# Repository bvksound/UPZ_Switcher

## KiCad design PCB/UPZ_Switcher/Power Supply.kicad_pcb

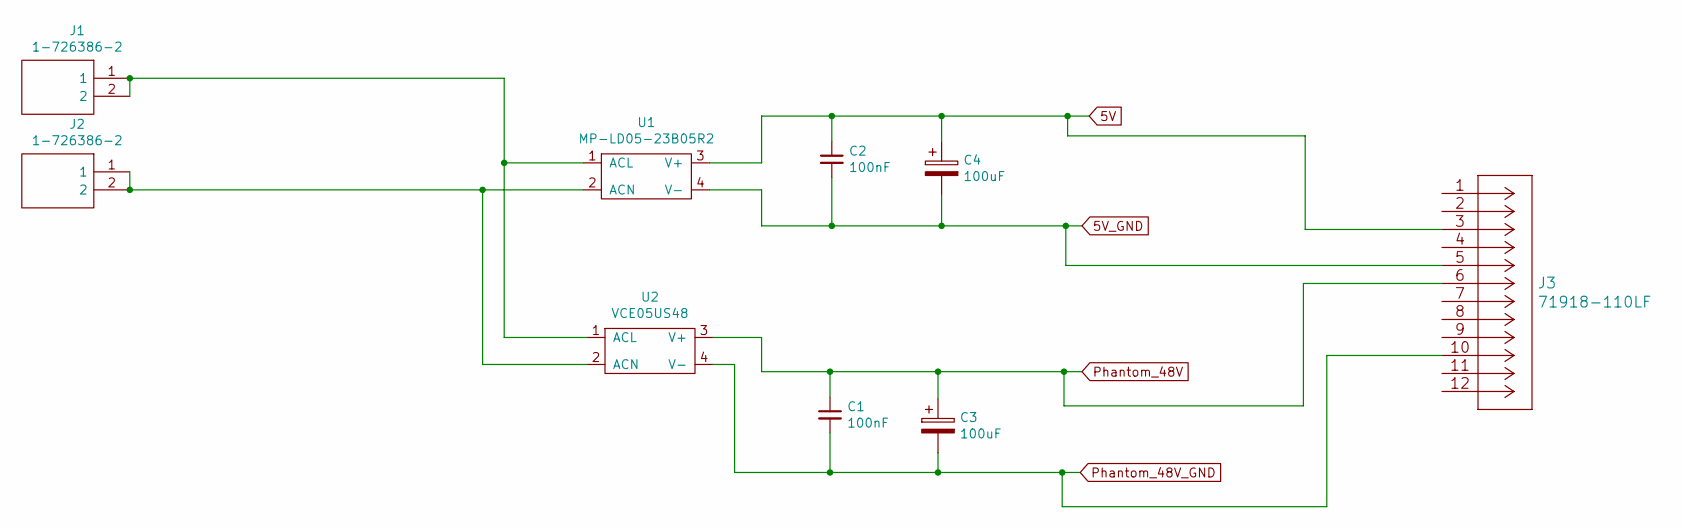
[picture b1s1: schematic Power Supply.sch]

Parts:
C1, C2: 100nF; C_1206_3216Metric
C3, C4: 100uF; CP_Radial_D10.0mm_P5.00mm
J1, J2: 1-726386-2; 17263862; Manufacturer_Part_Number 1-726386-2; Mouser Part Number 571-1-726386-2
J3: 71918-110LF
U1: MP-LD05-23B05R2
U2: VCE05US48

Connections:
5V: C2.1, C4.1, J3.3, U1.3 (V+)
5V_GND: C2.2, C4.2, J3.5, U1.4 (V-)
unnamed: J1.1, J1.2, U1.1 (ACL), U2.1 (ACL)
unnamed: J2.1, J2.2, U1.2 (ACN), U2.2 (ACN)
Phantom_48V: C1.1, C3.1, J3.6, U2.3 (V+)
Phantom_48V_GND: C1.2, C3.2, J3.10, U2.4 (V-)

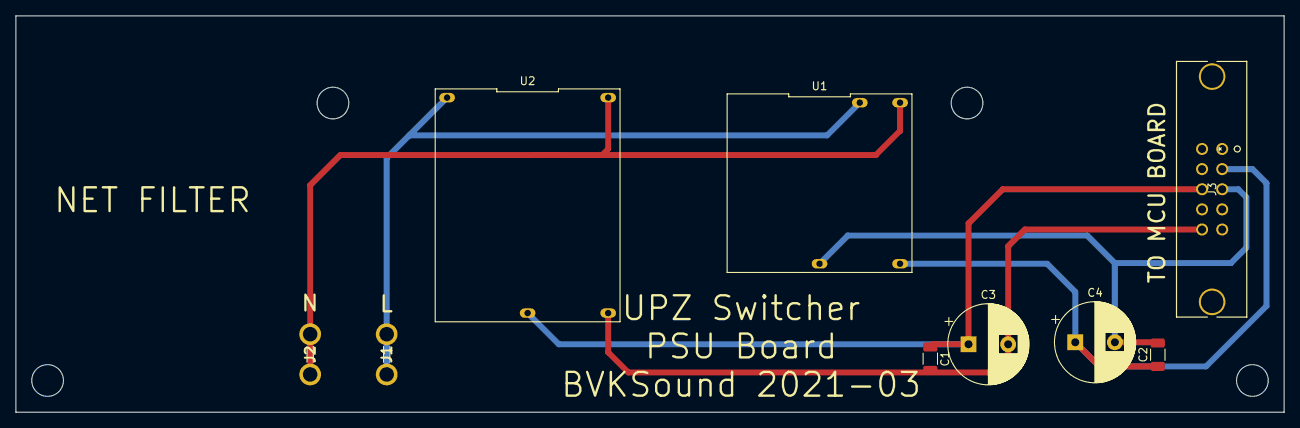
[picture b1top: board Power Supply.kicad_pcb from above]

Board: 2 copper layers, 160.0 x 50.0 mm, 9 parts (0 on the bottom side), 6 nets.

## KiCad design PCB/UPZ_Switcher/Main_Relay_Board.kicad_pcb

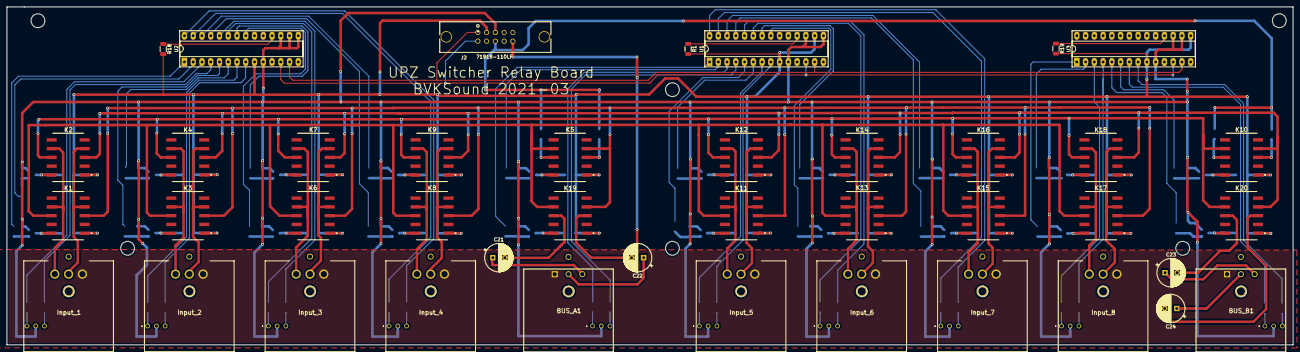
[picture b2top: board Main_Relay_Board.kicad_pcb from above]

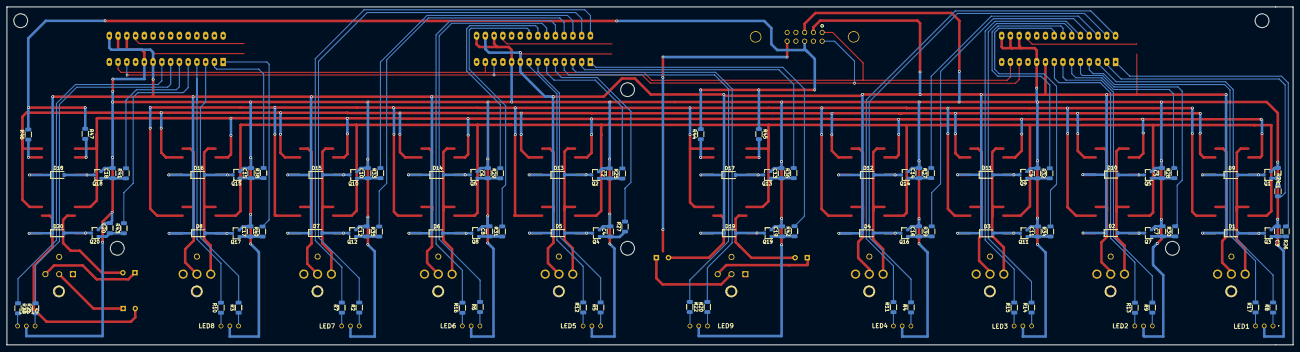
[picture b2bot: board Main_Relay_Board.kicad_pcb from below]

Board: 2 copper layers, 373.0 x 98.0 mm, 155 parts (105 on the bottom side), 141 nets.

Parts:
BUS_A1: NC3MD-H; NC3MDH
BUS_B1: NC3MD-H; NC3MDH
C1, C2, C3, C4, C5, C6, C7, C8, C9, C10, C11, C12, C13, C14, C15, C16, C17, C18, C19, C20: 10nF; C_1206_3216Metric
C21, C22, C23, C24: 47uF; CP_Radial_D8.0mm_P3.50mm
D1, D2, D3, D4, D5, D6, D7, D8, D9, D10, D11, D12, D13, D14, D15, D16, D17, D18, D19, D20: 1N4148W; D_SOD-123
Input_1, Input_2, Input_3, Input_4, Input_5, Input_6, Input_7, Input_8: NC3FDH
J2: 71918-110LF
K1, K2, K3, K4, K5, K6, K7, K8, K9, K10, K11, K12, K13, K14, K15, K16, K17, K18, K19, K20: TQ2SA-5V-Z; TQ2SAL23VZ
LED1, LED2, LED3, LED4, LED5, LED6, LED7, LED8, LED9, LED10: L-115WEGW; L115WEGW
Q1, Q2, Q3, Q4, Q5, Q6, Q7, Q8, Q9, Q10, Q11, Q12, Q13, Q14, Q15, Q16, Q17, Q18, Q19, Q20: BS170F; SOT-23
R1, R18, R19: 10K; R_1206_3216Metric
R2, R3, R4, R5, R6, R7, R8, R9, R10, R11, R12, R13, R14, R15, R16, R17, R20, R21, R22, R23: 100; R_1206_3216Metric
R24, R25, R26, R27, R28, R29, R30, R31, R32, R33, R34, R35, R36, R37, R38, R39, R40, R41, R42, R43: 1K; R_1206_3216Metric
R44, R45, R46, R47: 6K8; R_1206_3216Metric
U1, U2, U3: MCP23017_SP; DIP-28_W7.62mm_Socket_LongPads

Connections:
/Relay/BUSA.2: K1.8, K3.8, K5.7, K6.8, K8.8, K11.8, K13.8, K15.8, K17.8, K19.7
/Relay/BUSA.3: K1.3, K3.3, K5.4, K6.3, K8.3, K11.3, K13.3, K15.3, K17.3, K19.4
/Relay/BUSB.2: K2.8, K4.8, K7.8, K9.8, K10.7, K12.8, K14.8, K16.8, K18.8, K20.7
/Relay/BUSB.3: K2.3, K4.3, K7.3, K9.3, K10.4, K12.3, K14.3, K16.3, K18.3, K20.4
/Relay/IN1.2: Input_1.2, K1.7, K2.7
/Relay/IN1.3: Input_1.3, K1.4, K2.4
/Relay/IN2.2: Input_2.2, K3.7, K4.7
/Relay/IN2.3: Input_2.3, K3.4, K4.4
/Relay/IN3.2: Input_3.2, K6.7, K7.7
/Relay/IN3.3: Input_3.3, K6.4, K7.4
/Relay/IN4.2: Input_4.2, K8.7, K9.7
/Relay/IN4.3: Input_4.3, K8.4, K9.4
/Relay/IN5.2: Input_5.2, K11.7, K12.7
/Relay/IN5.3: Input_5.3, K11.4, K12.4
/Relay/IN6.2: Input_6.2, K13.7, K14.7
/Relay/IN6.3: Input_6.3, K13.4, K14.4
/Relay/IN7.2: Input_7.2, K15.7, K16.7
/Relay/IN7.3: Input_7.3, K15.4, K16.4
/Relay/IN8.2: Input_8.2, K17.7, K18.7
/Relay/IN8.3: Input_8.3, K17.4, K18.4
/Relay/OUTA.2: BUS_A1.2, C21.1
/Relay/OUTA.3: BUS_A1.3, C22.1
/Relay/OUTB.2: BUS_B1.2, C23.1
/Relay/OUTB.3: BUS_B1.3, C24.1
GND: C1.2, C2.2, C3.2, C4.2, C5.2, C6.2, C7.2, C8.2, C9.2, C10.2, C11.2, C12.2, C13.2, C14.2, C15.2, C16.2, C17.2, C18.2, C19.2, C20.2, J2.5, LED1.2, LED2.2, LED3.2, LED4.2, LED5.2, LED6.2, LED7.2, LED8.2, LED9.2, LED10.2, Q1.2, Q2.2, Q3.2, Q4.2, Q5.2, Q6.2, Q7.2, Q8.2, Q9.2, Q10.2, Q11.2, Q12.2, Q13.2, Q14.2, Q15.2, Q16.2, Q17.2, Q18.2, Q19.2, Q20.2, U1.10, U1.15, U1.17, U2.10, U2.15, U2.16, U2.17, U3.10, U3.16, U3.17
I2C_SCK: J2.2, U1.12, U2.12, U3.12
I2C_SDA: J2.1, U1.13, U2.13, U3.13
K1+: D1.1, D2.1, D3.1, D4.1, D5.1, D6.1, D7.1, D8.1, D9.1, D10.1, D11.1, D12.1, D13.1, D14.1, D15.1, D16.1, D17.1, D18.1, D19.1, D20.1, J2.3, K1.1, K2.1, K3.1, K4.1, K5.1, K6.1, K7.1, K8.1, K9.1, K10.1, K11.1, K12.1, K13.1, K14.1, K15.1, K16.1, K17.1, K18.1, K19.1, K20.1, R1.2, R18.2, R19.2, U1.9, U1.16, U2.9, U3.9, U3.15
K1-: D1.2, K1.10, Q3.3
K2-: D2.2, K3.10, Q7.3
K3-: D3.2, K6.10, Q11.3
K4-: D4.2, K8.10, Q16.3
K5-: D5.2, K11.10, Q4.3
K6-: D6.2, K13.10, Q8.3
K7-: D7.2, K15.10, Q12.3
K8-: D8.2, K17.10, Q17.3
K9-: D9.2, K2.10, Q1.3
K10-: D10.2, K4.10, Q5.3
K11-: D11.2, K7.10, Q9.3
K12-: D12.2, K9.10, Q14.3
K13-: D13.2, K12.10, Q2.3
K14-: D14.2, K14.10, Q6.3
K15-: D15.2, K16.10, Q10.3
K16-: D16.2, K18.10, Q15.3
K17-: D17.2, K5.10, Q13.3
K18-: D18.2, K10.10, Q18.3
K19-: D19.2, K19.10, Q19.3
K20-: D20.2, K20.10, Q20.3
MCP1.1: R26.2, U2.1
MCP1.2: R24.2, U2.2
MCP1.3: R8.2, U2.3
MCP1.4: R17.2, U2.4
MCP1.5: R30.2, U2.5
MCP1.6: R28.2, U2.6
MCP1.7: R9.2, U2.7
MCP1.8: R13.2, U2.8
MCP1.9: R34.2, U2.21
MCP1.10: R32.2, U2.22
MCP1.11: R14.2, U2.23
MCP1.12: R15.2, U2.24
MCP1.13: R39.2, U2.25
MCP1.14: R37.2, U2.26
MCP1.15: R4.2, U2.27
MCP1.16: R11.2, U2.28
MCP2.1: R42.2, U1.1
MCP2.2: R36.2, U1.2
MCP2.3: R20.2, U1.3
MCP2.4: R22.1, U1.4
MCP2.5: R27.2, U1.5
MCP2.6: R25.2, U1.6
MCP2.7: R5.2, U1.7
MCP2.8: R12.2, U1.8
MCP2.9: R31.2, U1.21
MCP2.10: R29.2, U1.22
MCP2.11: R6.2, U1.23
MCP2.12: R16.2, U1.24
MCP2.13: R35.2, U1.25
MCP2.14: R33.2, U1.26
MCP2.15: R2.2, U1.27
MCP2.16: R7.2, U1.28
MCP3.1: R40.2, U3.1
MCP3.2: R38.2, U3.2
MCP3.3: R3.2, U3.3
MCP3.4: R10.2, U3.4
MCP3.5: R43.2, U3.5
MCP3.6: R41.2, U3.6
MCP3.7: R21.2, U3.7
MCP3.8: R23.1, U3.8
unnamed: C1.1, Q1.1, R24.1
unnamed: C2.1, Q2.1, R25.1
unnamed: C3.1, Q3.1, R26.1
unnamed: C4.1, Q4.1, R27.1
unnamed: C5.1, Q5.1, R28.1
unnamed: C6.1, Q6.1, R29.1
unnamed: C7.1, Q7.1, R30.1
unnamed: C8.1, Q8.1, R31.1
unnamed: C9.1, Q9.1, R32.1
unnamed: C10.1, Q10.1, R33.1
unnamed: C11.1, Q11.1, R34.1
unnamed: C12.1, Q12.1, R35.1
unnamed: C13.1, Q13.1, R36.1
unnamed: C14.1, Q14.1, R37.1
unnamed: C15.1, Q15.1, R38.1
unnamed: C16.1, Q16.1, R39.1
unnamed: C17.1, Q17.1, R40.1
unnamed: C18.1, Q18.1, R41.1
unnamed: C19.1, Q19.1, R42.1
unnamed: C20.1, Q20.1, R43.1
unnamed: C21.2, K19.8
unnamed: C22.2, K19.3
unnamed: C23.2, K20.8
unnamed: C24.2, K20.3
unnamed: K5.3, R44.1
unnamed: K5.8, R45.2
unnamed: K10.3, R46.1
unnamed: K10.8, R47.2
unnamed: LED1.1, R8.1
unnamed: LED1.3, R17.1
unnamed: LED2.1, R9.1
unnamed: LED2.3, R13.1
unnamed: LED3.1, R14.1
unnamed: LED3.3, R15.1
unnamed: LED4.1, R4.1
unnamed: LED4.3, R11.1
unnamed: LED5.1, R5.1
unnamed: LED5.3, R12.1
unnamed: LED6.1, R6.1
unnamed: LED6.3, R16.1
unnamed: LED7.1, R2.1
unnamed: LED7.3, R7.1
unnamed: LED8.1, R3.1
unnamed: LED8.3, R10.1
unnamed: LED9.1, R20.1
unnamed: LED9.3, R22.2
unnamed: LED10.1, R21.1
unnamed: LED10.3, R23.2
unnamed: R1.1, U1.18
unnamed: R18.1, U2.18
unnamed: R19.1, U3.18
Phantom_48V: J2.6, R44.2, R45.1, R46.2, R47.1
Phantom_48V_GND: BUS_A1.1, BUS_B1.1, Input_1.1, Input_2.1, Input_3.1, Input_4.1, Input_5.1, Input_6.1, Input_7.1, Input_8.1, J2.10

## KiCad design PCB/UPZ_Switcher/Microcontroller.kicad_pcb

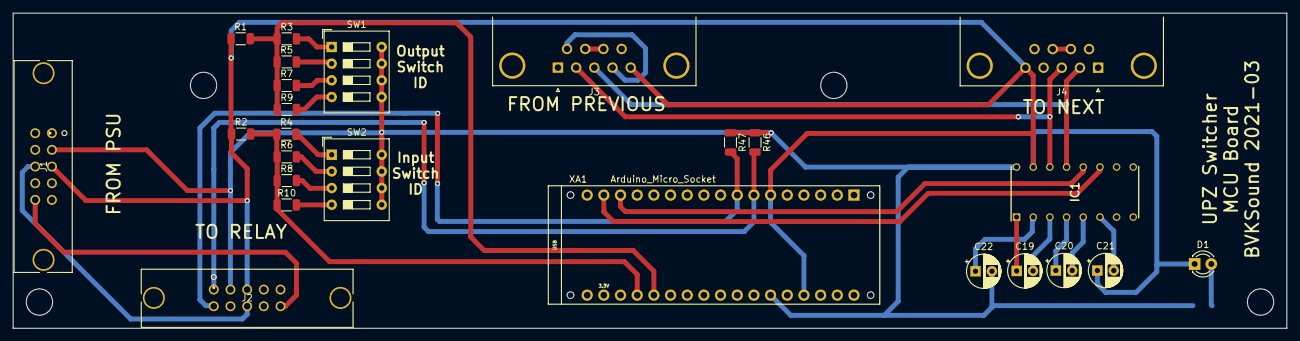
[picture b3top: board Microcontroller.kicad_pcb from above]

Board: 2 copper layers, 194.0 x 48.0 mm, 26 parts (1 on the bottom side), 30 nets.

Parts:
C19, C20, C21, C22: 1uF; CP_Radial_D5.0mm_P2.50mm
D1: LED; LED_D3.0mm
IC1: MAX232ECPE+; DIP762W56P254L1918H457Q16N
J1: FROM PSU; 71918-110LF
J2: TO RELAY; 71918-110LF
J3: FROM PREVIOUS; DSUB-9_Female_Horizontal_P2.77x2.84mm_EdgePinOffset4.94mm_H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
J4: TO NEXT; DSUB-9_Male_Horizontal_P2.77x2.84mm_EdgePinOffset4.94mm_Hou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
R1, R2, R3, R4: 10K; R_1206_3216Metric
R5, R6: 20K; R_1206_3216Metric
R7, R8: 40K; R_1206_3216Metric
R9, R10: 80K; R_1206_3216Metric
R11: 100; R_1206_3216Metric
R46, R47: 4K7; R_1206_3216Metric
SW1, SW2: SW_DIP_x04; SW_DIP_SPSTx04_Slide_9.78x12.34mm_W7.62mm_P2.54mm
XA1: Arduino_Micro_Socket

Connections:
/5V: C22.2, IC1.16, J1.3, J2.3, R11.1, R46.1, R47.1, SW1.5, SW1.6, SW1.7, SW1.8, SW2.5, SW2.6, SW2.7, SW2.8, XA1.5V
/I2C_SCK: J2.2, R47.2, XA1.D3
/I2C_SDA: J2.1, R46.2, XA1.D2
GND: C21.1, D1.1, IC1.15, J1.5, J2.5, J3.5, J4.5, R1.1, R2.1, XA1.GND1, XA1.GND2
unnamed: C19.1, IC1.1
unnamed: C19.2, IC1.3
unnamed: C20.1, IC1.4
unnamed: C20.2, IC1.5
unnamed: C21.2, IC1.6
unnamed: C22.1, IC1.2
unnamed: D1.2, R11.2
unnamed: IC1.11, XA1.D11
unnamed: IC1.12, XA1.D10
unnamed: IC1.13, J3.3, J4.2
unnamed: IC1.14, J3.2, J4.3
unnamed: J1.6, J2.6
unnamed: J1.10, J2.10
unnamed: J3.4, J3.6
unnamed: J3.7, J3.8
unnamed: J4.7, J4.8
unnamed: R1.2, R3.1, R5.1, R7.1, R9.1, XA1.A1
unnamed: R3.2, SW1.1
unnamed: R4.2, SW2.1
unnamed: R5.2, SW1.2
unnamed: R6.2, SW2.2
unnamed: R7.2, SW1.3
unnamed: R8.2, SW2.3
unnamed: R9.2, SW1.4
unnamed: R2.2, R4.1, R6.1, R8.1, R10.1, XA1.A0
unnamed: R10.2, SW2.4

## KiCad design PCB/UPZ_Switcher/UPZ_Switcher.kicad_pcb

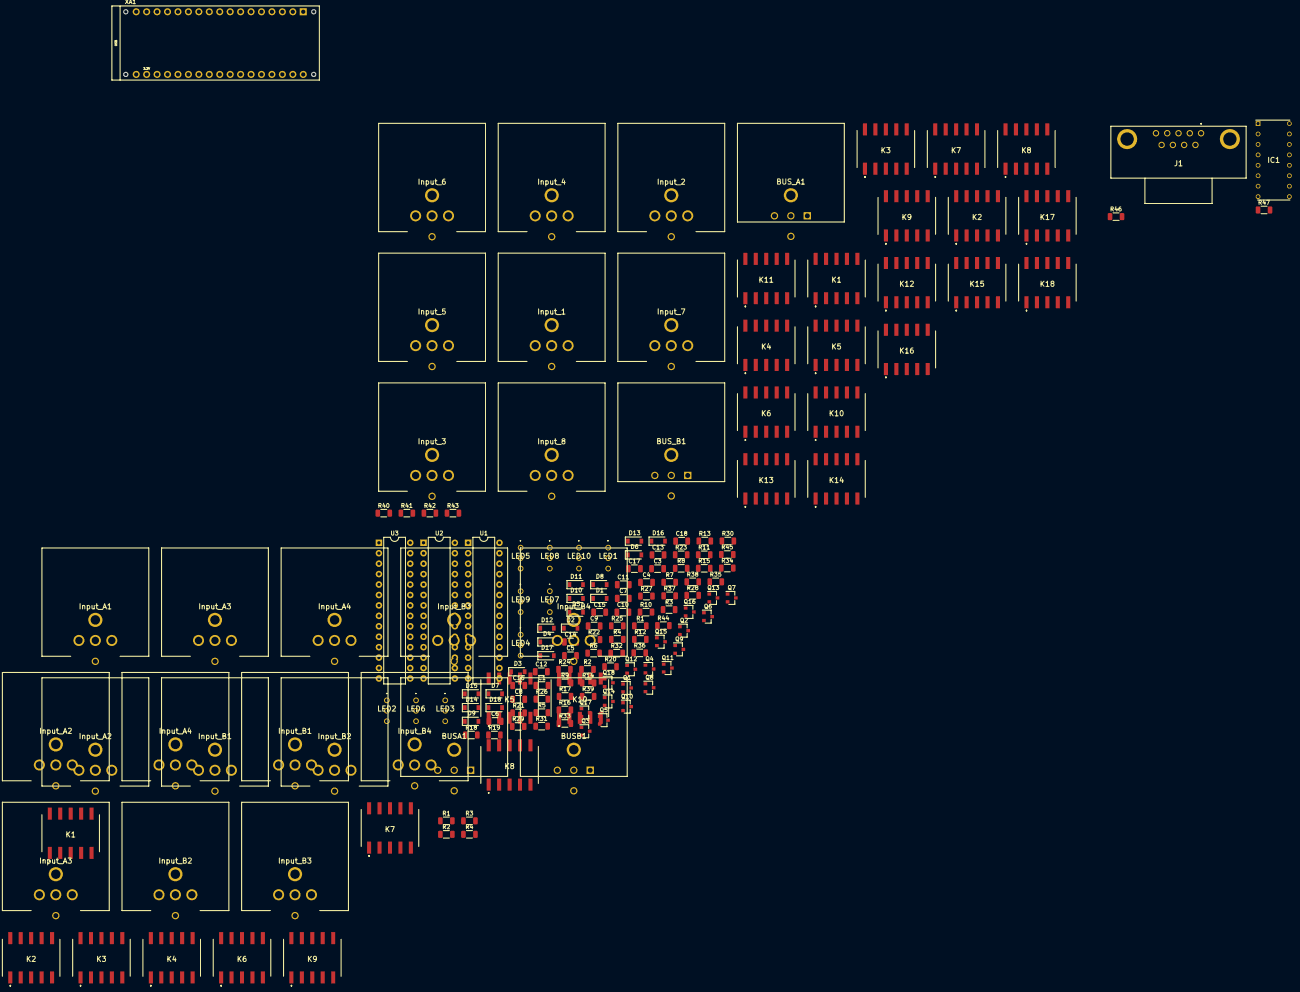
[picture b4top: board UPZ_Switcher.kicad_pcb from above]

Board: 2 copper layers, 175 parts (0 on the bottom side), 197 nets, no tracks yet.

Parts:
BUSA1: NC3MD-H; NC3MDH
BUSB1: NC3MD-H; NC3MDH
BUS_A1: NC3MD-H; NC3MDH
BUS_B1: NC3MD-H; NC3MDH
C1, C3, C4, C5, C6, C7, C8, C9, C10, C11, C12, C13, C14, C15, C16, C17, C18: 10nF; C_1206_3216Metric
D1, D2, D3, D4, D5, D6, D7, D8, D9, D10, D11, D12, D13, D14, D15, D16, D17, D18: 1N4148W; D_SOD-123
IC1: MAX232ECPE+; DIP762W56P254L1918H457Q16N
Input_1, Input_2, Input_3, Input_4, Input_5, Input_6, Input_7, Input_8: NC3FDH
Input_A1, Input_A2, Input_A2#2, Input_A3, Input_A3#2, Input_A4, Input_A4#2: NC3FDH
Input_B1, Input_B1#2, Input_B2, Input_B2#2, Input_B3, Input_B3#2, Input_B4, Input_B4#2: NC3FDH
J1: 5747844-6; 57478446
K1, K1#2, K2, K2#2, K3, K3#2, K4, K4#2, K5, K5#2, K6, K6#2, K7, K7#2, K8, K8#2, K9, K9#2, K10, K10#2, K11, K12, K13, K14, K15, K16, K17, K18: TQ2SA-5V-Z; TQ2SAL23VZ
LED1, LED2, LED3, LED4, LED5, LED6, LED7, LED8, LED9, LED10: L-115WEGW; L115WEGW
Q1, Q2, Q3, Q4, Q5, Q6, Q7, Q8, Q9, Q10, Q11, Q12, Q13, Q14, Q15, Q16, Q17, Q18: BS170F; SOT-23
R1, R2, R3, R4, R5, R6, R7, R8, R9, R10, R11, R12, R13, R14, R15, R16, R17, R18: 1K; R_1206_3216Metric
R1#2, R2#2, R3#2, R4#2, R40, R41, R42, R43: 6K8; R_1206_3216Metric
R19, R20, R21, R22, R23, R24, R25, R26, R27, R28, R29, R30, R31, R32, R33, R34, R35, R36, R37, R38: 100; R_1206_3216Metric
R39, R44, R45: 10K; R_1206_3216Metric
R46, R47: 4K7; R_1206_3216Metric
U1, U2, U3: MCP23017_SP; DIP-28_W7.62mm
XA1: Arduino_Micro_Socket

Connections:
/IO Board/5V_Relay: D1.1, D2.1, D3.1, D4.1, D5.1, D6.1, D7.1, D8.1, D9.1, D10.1, D11.1, D12.1, D13.1, D14.1, D15.1, D16.1, D17.1, D18.1
/IO Board/I2C_SCK: R47.2, U1.12, U2.12, U3.12, XA1.D3
/IO Board/I2C_SDA: R46.2, U1.13, U2.13, U3.13, XA1.D2
/IO Board/K1-: D1.2, Q1.3
/IO Board/K2-: D2.2, Q2.3
/IO Board/K3-: D3.2, Q3.3
/IO Board/K4-: D4.2, Q4.3
/IO Board/K5-: D5.2, Q5.3
/IO Board/K6-: D6.2, Q6.3
/IO Board/K7-: D7.2, Q7.3
/IO Board/K8-: D8.2, Q8.3
/IO Board/K9-: D9.2, Q9.3
/IO Board/K10-: D10.2, Q10.3
/IO Board/K11-: D11.2, Q11.3
/IO Board/K12-: D12.2, Q12.3
/IO Board/K13-: D13.2, Q13.3
/IO Board/K14-: D14.2, Q14.3
/IO Board/K15-: D15.2, Q15.3
/IO Board/K16-: D16.2, Q16.3
/IO Board/K17-: D17.2, Q17.3
/IO Board/K18-: D18.2, Q18.3
/IO Board/VDD: R39.2, R44.2, R45.2, U1.9, U2.9, U3.9
/MicroController Board/5V: IC1.16, R46.1, R47.1, XA1.5V
/Relay Board/BUSA.2: BUS_A1.2, K1.3, K3.3, K5.4, K6.3, K8.3, K11.3, K13.3, K15.3, K17.3
/Relay Board/BUSA.3: BUS_A1.3, K1.8, K3.8, K5.7, K6.8, K8.8, K11.8, K13.8, K15.8, K17.8
/Relay Board/BUSB.2: BUS_B1.2, K2.3, K4.3, K7.3, K9.3, K10.4, K12.3, K14.3, K16.3, K18.3
/Relay Board/BUSB.3: BUS_B1.3, K2.8, K4.8, K7.8, K9.8, K10.7, K12.8, K14.8, K16.8, K18.8
/Relay Board/IN1.2: Input_1.2, K1.4, K2.4
/Relay Board/IN1.3: Input_1.3, K1.7, K2.7
/Relay Board/IN2.2: Input_2.2, K3.4, K4.4
/Relay Board/IN2.3: Input_2.3, K3.7, K4.7
/Relay Board/IN3.2: Input_3.2, K6.4, K7.4
/Relay Board/IN3.3: Input_3.3, K6.7, K7.7
/Relay Board/IN4.2: Input_4.2, K8.4, K9.4
/Relay Board/IN4.3: Input_4.3, K8.7, K9.7
/Relay Board/IN5.2: Input_5.2, K11.4, K12.4
/Relay Board/IN5.3: Input_5.3, K11.7, K12.7
/Relay Board/IN6.2: Input_6.2, K13.4, K14.4
/Relay Board/IN6.3: Input_6.3, K13.7, K14.7
/Relay Board/IN7.2: Input_7.2, K15.4, K16.4
/Relay Board/IN7.3: Input_7.3, K15.7, K16.7
/Relay Board/IN8.2: Input_8.2, K17.4, K18.4
/Relay Board/IN8.3: Input_8.3, K17.7, K18.7
/Relay Board/Phantom_48V: R40.2, R41.1, R42.2, R43.1
/RelayBoard/A1.2: Input_A1.2, K1#2.4
/RelayBoard/A1.3: Input_A1.3, K1#2.7
/RelayBoard/A2.2: Input_A2.2, K2#2.4
/RelayBoard/A2.3: Input_A2.3, K2#2.7
/RelayBoard/A3.2: Input_A3.2, K3#2.4
/RelayBoard/A3.3: Input_A3.3, K3#2.7
/RelayBoard/A4.2: Input_A4.2, K4#2.4
/RelayBoard/A4.3: Input_A4.3, K4#2.7
/RelayBoard/B1.2: Input_B1.2, K5#2.4
/RelayBoard/B1.3: Input_B1.3, K5#2.7
/RelayBoard/B2.2: Input_B2.2, K6#2.4
/RelayBoard/B2.3: Input_B2.3, K6#2.7
/RelayBoard/B3.2: Input_B3.2, K7#2.4
/RelayBoard/B3.3: Input_B3.3, K7#2.7
/RelayBoard/B4.2: Input_B4.2, K8#2.4
/RelayBoard/B4.3: Input_B4.3, K8#2.7
/RelayBoard/BUSB.2: K5#2.3, K6#2.3, K7#2.3, K8#2.3, K10#2.4
/RelayBoard/BUSB.3: K5#2.8, K6#2.8, K7#2.8, K8#2.8, K10#2.7
/RelayBoard/Phantom_48V: R1#2.2, R2#2.1, R3#2.2, R4#2.1
BUSA.2: BUSA1.2, K1#2.3, K2#2.3, K3#2.3, K4#2.3, K9#2.4
BUSA.3: BUSA1.3, K1#2.8, K2#2.8, K3#2.8, K4#2.8, K9#2.7
GND: BUSA1.1, BUS_A1.1, BUS_B1.1, C1.2, C3.2, C4.2, C5.2, C6.2, C7.2, C8.2, C9.2, C10.2, C11.2, C12.2, C13.2, C14.2, C15.2, C16.2, C17.2, C18.2, IC1.15, J1.5, LED1.2, LED2.2, LED3.2, LED4.2, LED5.2, LED6.2, LED7.2, LED8.2, LED9.2, LED10.2, Q1.2, Q2.2, Q3.2, Q4.2, Q5.2, Q6.2, Q7.2, Q8.2, Q9.2, Q10.2, Q11.2, Q12.2, Q13.2, Q14.2, Q15.2, Q16.2, Q17.2, Q18.2, U1.10, U2.10, U3.10, XA1.GND1, XA1.GND2
unnamed: C1.1, Q1.1, R1.1
unnamed: Q2.1, R2.1
unnamed: C3.1, Q3.1, R3.1
unnamed: C4.1, Q4.1, R4.1
unnamed: C5.1, Q5.1, R5.1
unnamed: C6.1, Q6.1, R6.1
unnamed: C7.1, Q7.1, R7.1
unnamed: C8.1, Q8.1, R8.1
unnamed: C9.1, Q9.1, R9.1
unnamed: C10.1, Q10.1, R10.1
unnamed: C11.1, Q11.1, R11.1
unnamed: C12.1, Q12.1, R12.1
unnamed: C13.1, Q13.1, R13.1
unnamed: C14.1, Q14.1, R14.1
unnamed: C15.1, Q15.1, R15.1
unnamed: C16.1, Q16.1, R16.1
unnamed: C17.1, Q17.1, R17.1
unnamed: C18.1, Q18.1, R18.1
unnamed: IC1.11, XA1.D1
unnamed: IC1.12, XA1.D0
unnamed: IC1.13, J1.3
unnamed: IC1.14, J1.2
unnamed: J1.4, J1.6
unnamed: J1.7, J1.8
unnamed: K1.2, K1#2.2
unnamed: K1.5, K1#2.5
unnamed: K1.6, K1#2.6
unnamed: K1.9, K1#2.9
unnamed: K2.2, K2#2.2
unnamed: K2.5, K2#2.5
unnamed: K2.6, K2#2.6
unnamed: K2.9, K2#2.9
unnamed: K3.2, K3#2.2
unnamed: K3.5, K3#2.5
unnamed: K3.6, K3#2.6
unnamed: K3.9, K3#2.9
unnamed: K4.2, K4#2.2
unnamed: K4.5, K4#2.5
unnamed: K4.6, K4#2.6
unnamed: K4.9, K4#2.9
unnamed: K5.2, K5#2.2
unnamed: K5.3, R40.1
unnamed: K5.5, K5#2.5
unnamed: K5.6, K5#2.6
unnamed: K5.8, R41.2
unnamed: K5.9, K5#2.9
unnamed: K6.2, K6#2.2
unnamed: K6.5, K6#2.5
unnamed: K6.6, K6#2.6
unnamed: K6.9, K6#2.9
unnamed: K7.2, K7#2.2
unnamed: K7.5, K7#2.5
unnamed: K7.6, K7#2.6
unnamed: K7.9, K7#2.9
unnamed: K8.2, K8#2.2
unnamed: K8.5, K8#2.5
unnamed: K8.6, K8#2.6
unnamed: K8.9, K8#2.9
unnamed: K9.2, K9#2.2
unnamed: K9#2.3, R1#2.1
unnamed: K9.5, K9#2.5
unnamed: K9.6, K9#2.6
unnamed: K9#2.8, R2#2.2
unnamed: K9.9, K9#2.9
unnamed: K10.2, K10#2.2
unnamed: K10.3, K10#2.3, R3#2.1, R42.1
unnamed: K10.5, K10#2.5
unnamed: K10.6, K10#2.6
unnamed: K10.8, K10#2.8, R4#2.2, R43.2
unnamed: K10.9, K10#2.9
unnamed: LED1.1, R23.1
unnamed: LED1.3, R24.1
unnamed: LED2.1, R25.1
unnamed: LED2.3, R26.1
unnamed: LED3.1, R27.1
unnamed: LED3.3, R28.1
unnamed: LED4.1, R29.1
unnamed: LED4.3, R30.1
unnamed: LED5.1, R31.1
unnamed: LED5.3, R32.1
unnamed: LED6.1, R33.1
unnamed: LED6.3, R34.1
unnamed: LED7.1, R35.1
unnamed: LED7.3, R36.1
unnamed: LED8.1, R37.1
unnamed: LED8.3, R38.1
unnamed: LED9.1, R19.1
unnamed: LED9.3, R20.2
unnamed: LED10.1, R21.1
unnamed: LED10.3, R22.2
unnamed: R1.2, U1.1
unnamed: R2.2, U1.2
unnamed: R3.2, U1.3
unnamed: R4.2, U1.4
unnamed: R5.2, U1.5
unnamed: R6.2, U1.6
unnamed: R7.2, U1.7
unnamed: R8.2, U1.8
unnamed: R9.2, U1.21
unnamed: R10.2, U1.22
unnamed: R11.2, U1.23
unnamed: R12.2, U1.24
unnamed: R13.2, U1.25
unnamed: R14.2, U1.26
unnamed: R15.2, U1.27
unnamed: R16.2, U1.28
unnamed: R17.2, U2.1
unnamed: R18.2, U2.2
unnamed: R19.2, U2.25
unnamed: R20.1, U2.26
unnamed: R21.2, U2.27
unnamed: R22.1, U2.28
unnamed: R23.2, U3.1
unnamed: R24.2, U3.2
unnamed: R25.2, U3.3
unnamed: R26.2, U3.4
unnamed: R27.2, U3.5
unnamed: R28.2, U3.6
unnamed: R29.2, U3.7
unnamed: R30.2, U3.8
unnamed: R31.2, U3.21
unnamed: R32.2, U3.22
unnamed: R33.2, U3.23
unnamed: R34.2, U3.24
unnamed: R35.2, U3.25
unnamed: R36.2, U3.26
unnamed: R37.2, U3.27
unnamed: R38.2, U3.28
unnamed: R39.1, U3.18
unnamed: R44.1, U1.18
unnamed: R45.1, U2.18

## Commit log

2021-02-26 Start
    Draft Bom
2021-02-28 Draft schematics added
2021-03-06 Updated schematic, PSU added + draft program
2021-03-06 functions added, taking shape
2021-03-07 update before refactoring code for cleanup
2021-03-07 Draft release finished
2021-03-12 Started PCB design
2021-03-13 Relay Board finished
2021-03-13 updated phantom design + MCU board
2021-03-16 update on power supply
2021-03-26 final
2021-03-27 fix in gerber files
2021-04-08 Update UPZ_Switcher.ino
    bugfixes
2021-04-11 Update in Phantom Led Blinking

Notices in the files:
parts and their libraries:
Copyright 2016 Accelerated Designs. All rights reserved.
